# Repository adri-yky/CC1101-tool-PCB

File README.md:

La PCB es mia, el codigo es de:
(C) Adam Loboda '2023 , adam.loboda@wp.pl
based on great SmartRC library by Little_S@tan

<h1>MATERIALES</h1>
- x1 16v 100nF <br>
- x1 16v 1uF <br>
- x1 ESP32 C3 supermini

Los condensadores puedes soldarlos en el orden que quieras, se puede usar tambien sin condensador pero conviene soldarlos para filtrar interferencias.

<h1 style="color: red; font-weight: 800;">IMPORTANTE!!</h1>
<p style="color: red;">
  Vale, la plaquita esta guay lo unico que tengo que arreglar los condensadores que hay porque falla el tamaño de los SMD (Cosa que arreglare en un futuro)
  El tamaño deberia ser 0402 pero no es correcto del todo
</p>

<h1>DIY</h1>
Si alguien quiere recrearlo por su cuenta sin PCB estos son los pines

```
byte sck = 4;   // GPIO 4
byte miso = 5;  // GPIO 5
byte mosi = 6; // GPIO 6
byte ss = 7;   // GPIO 7
int gdo0 = 0;  // GPIO 0
int gdo2 = 1;   // GPIO 1
```
Los pines corresponden a los GPIOS del ESP32 c3 supermini
Estos son los del CC1101:

<h1>CONECTAR</h1>
Para conectar puedes usar cualquier terminal en serie, en PC puedes usar putty y en android SerialUSB terminal

<h1>COMANDOS</h1>

```
setmodulation <mode>         // set modulation mode. 0 = 2-FSK, 1 = GFSK, 2 = ASK/OOK, 3 = 4-FSK, 4 = MSK. 

setmhz <frequency>           // Here you can set your basic frequency. default = 433.92).The cc1101 can: 300-348 MHZ, 387-464MHZ and 779-928MHZ.

setdeviation <deviation>     // Set the Frequency deviation in kHz. Value from 1.58 to 380.85. Default is 47.60 kHz.

setchannel <channel>         // Set the Channelnumber from 0 to 255. Default is cahnnel 0.

setchsp <spacing>            // The channel spacing is multiplied by the channel number CHAN and added to the base frequency in kHz. Value from 25.39 to 405.45. Default is 199.95 kHz. 

setrxbw <Receive bandwidh>   // Set the Receive Bandwidth in kHz. Value from 58.03 to 812.50. Default is 812.50 kHz.

setdrate <datarate>          // Set the Data Rate in kBaud. Value from 0.02 to 1621.83. Default is 99.97 kBaud!

setpa <power value>          // Set TxPower. The following settings are possible depending on the frequency band.  (-30  -20  -15  -10  -6    0    5    7    10   11   12) Default is max!

setsyncmode  <sync mode>     // Combined sync-word qualifier mode. 0 = No preamble/sync. 1 = 16 sync word bits detected. 2 = 16/16 sync word bits detected. 3 = 30/32 sync word bits detected. 4 = No preamble/sync, carrier-sense above threshold. 5 = 15/16 + carrier-sense above threshold. 6 = 16/16 + carrier-sense above threshold. 7 = 30/32 + carrier-sense above threshold.

setsyncword <LOW, HIGH>      // Set sync word. Must be the same for the transmitter and receiver. (Syncword high, Syncword low)

setadrchk <address check>    // Controls address check configuration of received packages. 0 = No address check. 1 = Address check, no broadcast. 2 = Address check and 0 (0x00) broadcast. 3 = Address check and 0 (0x00) and 255 (0xFF) broadcast.

setaddr <address>            // Address used for packet filtration. Optional broadcast addresses are 0 (0x00) and 255 (0xFF).

setwhitedata <whitening>     // Turn data whitening on / off. 0 = Whitening off. 1 = Whitening on.

setpktformat <pkt format>    // Format of RX and TX data. 0 = Normal mode, use FIFOs for RX and TX. 1 = Synchronous serial mode, Data in on GDO0 and data out on either of the GDOx pins. 2 = Random TX mode; sends random data using PN9 generator. Used for test. Works as normal mode, setting 0 (00), in RX. 3 = Asynchronous serial mode, Data in on GDO0 and data out on either of the GDOx pins.

setlengthconfig <mode>       // 0 = Fixed packet length mode. 1 = Variable packet length mode. 2 = Infinite packet length mode. 3 = Reserved 

setpacketlength <mode>       // Indicates the packet length when fixed packet length mode is enabled. If variable packet length mode is used, this value indicates the maximum packet length allowed.

setcrc <mode>                // 1 = CRC calculation in TX and CRC check in RX enabled. 0 = CRC disabled for TX and RX.

setcrcaf <mode>             // Enable automatic flush of RX FIFO when CRC is not OK. This requires that only one packet is in the RXIFIFO and that packet length is limited to the RX FIFO size.

setdcfilteroff <mode>        // Disable digital DC blocking filter before demodulator. Only for data rates ≤ 250 kBaud The recommended IF frequency changes when the DC blocking is disabled. 1 = Disable (current optimized). 0 = Enable (better sensitivity).

setmanchester <mode>         // Enables Manchester encoding/decoding. 0 = Disable. 1 = Enable.

setfec <mode>                // Enable Forward Error Correction (FEC) with interleaving for packet payload (Only supported for fixed packet length mode. 0 = Disable. 1 = Enable.

setpre <mode>                // Sets the minimum number of preamble bytes to be transmitted. Values: 0 : 2, 1 : 3, 2 : 4, 3 : 6, 4 : 8, 5 : 12, 6 : 16, 7 : 24

setpqt <mode>                // Preamble quality estimator threshold. The preamble quality estimator increases an internal counter by one each time a bit is received that is different from the previous bit, and decreases the counter by 8 each time a bit is received that is the same as the last bit. A threshold of 4∙PQT for this counter is used to gate sync word detection. When PQT=0 a sync word is always accepted.

setappendstatus <mode>       // When enabled, two status bytes will be appended to the payload of the packet. The status bytes contain RSSI and LQI values, as well as CRC OK.

getrssi                      // Shows radio quality information about last received RF data frame.

scan <start freq> <end freq> // Scan frequency range for the highest signal and display results

rx                           // Enable or disable printing of received RF packets on serial terminal.

tx  <hex-vals>               // Send the packet of max 60 bytes < hex values > hex values over RF 

jam                          // Enable or disable continous jamming on selected band with selected modulation etc... 

brute <usec> <nb-of-bits>    // Brute force garage gate with <number-of-bits> keyword where symbol length is <microseconds>

rec                          // Enable or disable recording frames in the buffer.

show                         // Show content of recording buffer

add <hex-vals>               // Manually add single frame payload (max 60 hex values) to the buffer so it can be replayed

flush                        // Clear the recording buffer

play <N>                     // Replay 0 = all frames or N-th recorded frame

rxraw <microseconds>         // Sniffs radio by sampling with <microsecond> interval and prints received bytes in hex

addraw <hex-vals>            // Manually add chunks (max 60 hex values) to the buffer so they can be further replayed.

recraw <microseconds>        // Recording RAW RF data with <microsecond> sampling interval

showraw                      // Showing content of recording buffer in RAW format

showbit                      // Showing content of recording buffer in RAW format as a stream of bits.

playraw <microseconds>       // Replaying previously recorded RAW RF data with <microsecond> sampling interval

save                         // Store recording buffer content in non-volatile memory

load                         // Load the content from non-volatile memory to the recording buffer

echo <mode>                  // Enable or disable Echo on serial terminal. 1 = enabled, 0 = disabled

chat                         // switching device into chat mode 

x                            // Stops activities like jamming/receiving/recording packets

init                         // Restarts CC1101 board with default parameters
```

<h1>IMAGENES</h1>
<div style="text-align: center; align-items: center; display: flex;">

</div>

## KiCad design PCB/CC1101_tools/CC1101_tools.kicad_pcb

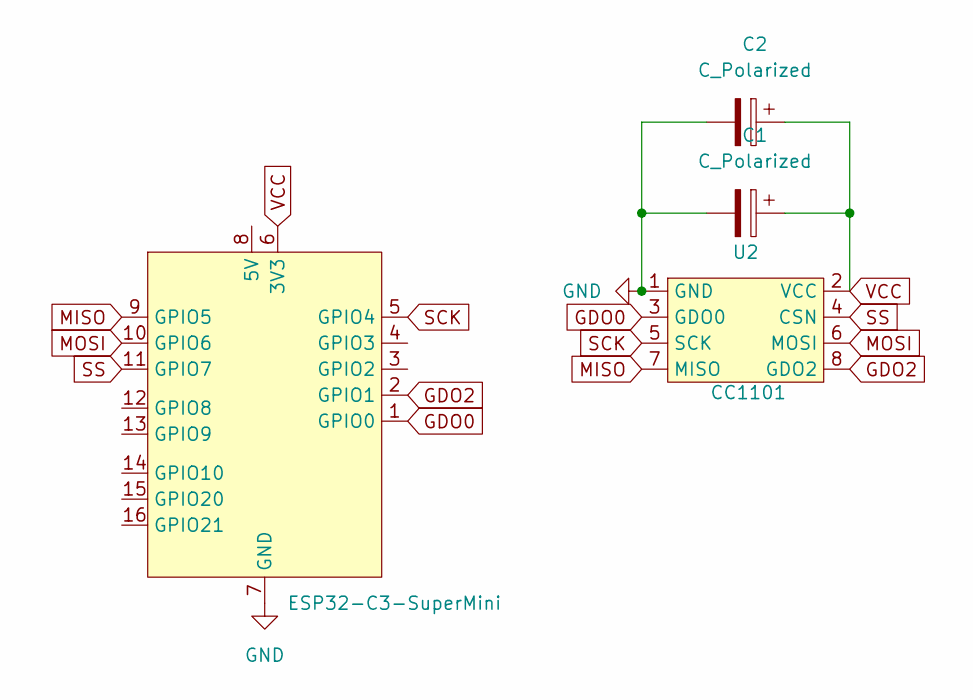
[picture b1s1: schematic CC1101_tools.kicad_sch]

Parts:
C1, C2: C_Polarized; C_01005_0402Metric
U1: ESP32-C3-SuperMini
U2: CC1101; CC1101c

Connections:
GDO0: U1.1 (GPIO0), U2.3 (GDO0)
GDO2: U1.2 (GPIO1), U2.8 (GDO2)
GND: C1.2, C2.2, U1.7 (GND), U2.1 (GND)
MISO: U1.9 (GPIO5), U2.7 (MISO)
MOSI: U1.10 (GPIO6), U2.6 (MOSI)
SCK: U1.5 (GPIO4), U2.5 (SCK)
SS: U1.11 (GPIO7), U2.4 (CSN)
VCC: C1.1, C2.1, U1.6 (3V3), U2.2 (VCC)

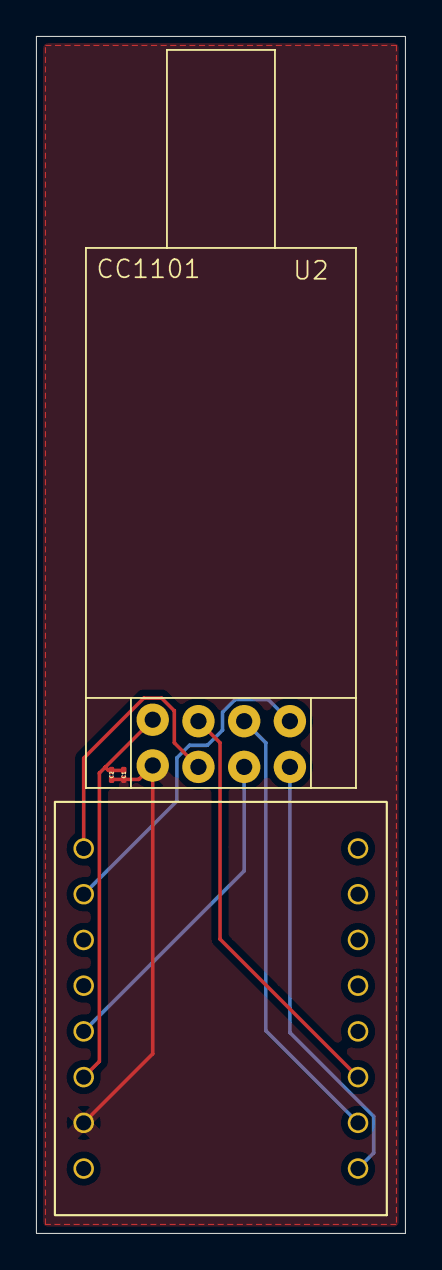
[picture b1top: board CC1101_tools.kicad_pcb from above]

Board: 2 copper layers, 20.5 x 66.5 mm, 4 parts (0 on the bottom side), 8 nets.
